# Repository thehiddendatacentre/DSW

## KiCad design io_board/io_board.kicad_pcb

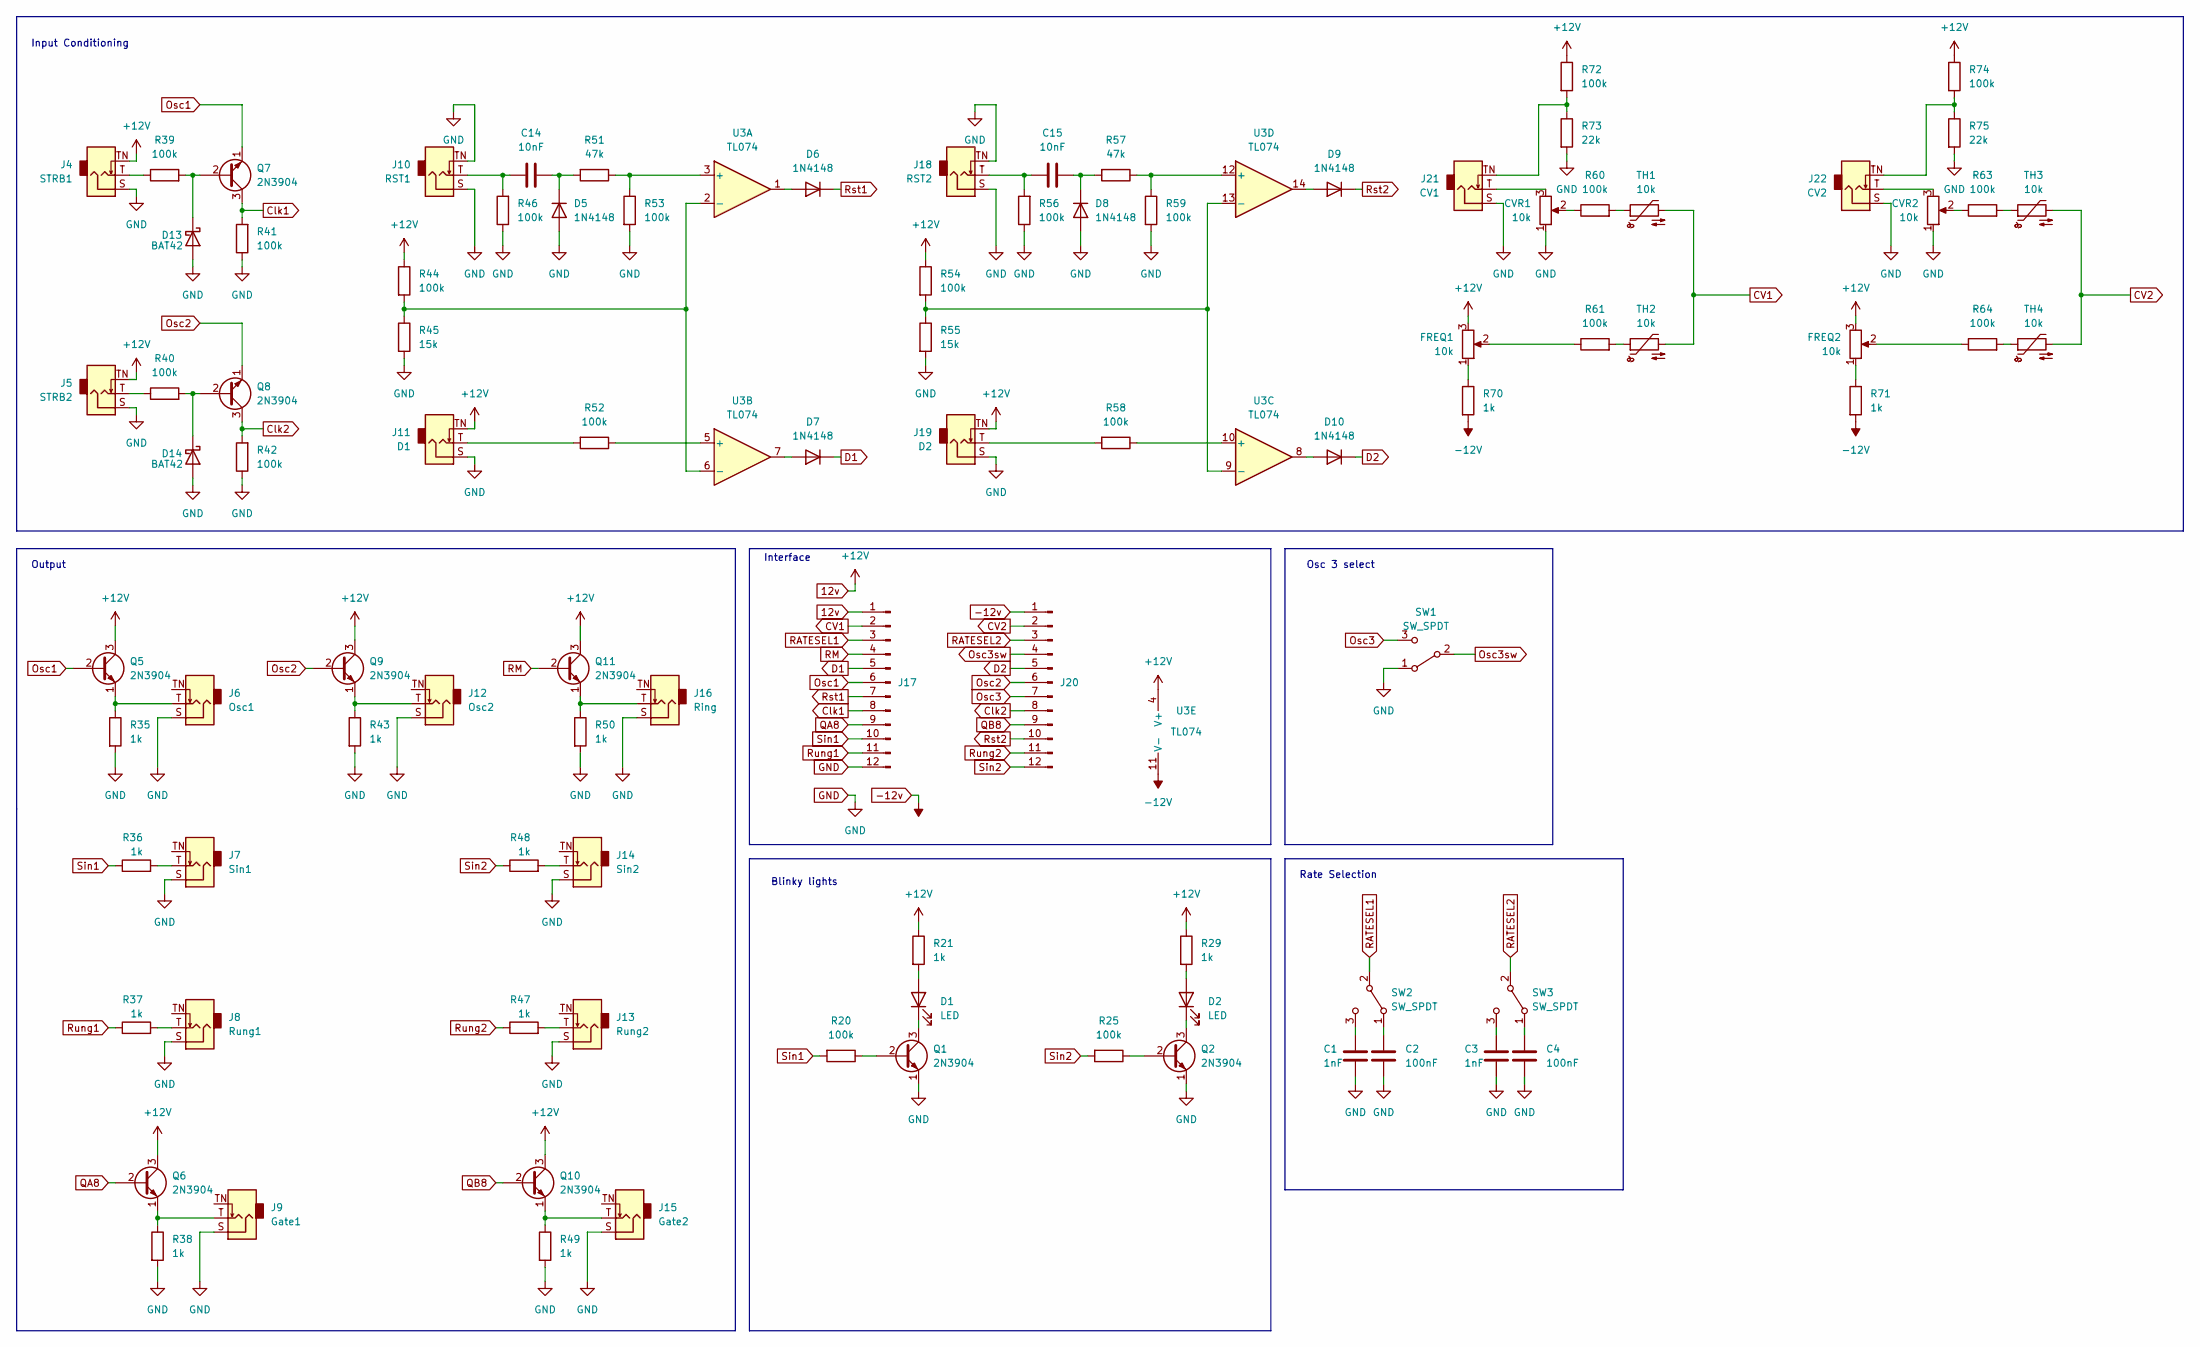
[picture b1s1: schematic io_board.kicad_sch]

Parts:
C1, C3: 1nF; C_Disc_D5.0mm_W2.5mm_P2.50mm
C2, C4: 100nF; C_Disc_D5.0mm_W2.5mm_P2.50mm
C14, C15: 10nF; C_Disc_D5.0mm_W2.5mm_P2.50mm
CVR1, CVR2: 10k; Potentiometer_Alpha_R0904N
D1, D2: LED; LED_D3.0mm
D5, D6, D7, D8, D9, D10: 1N4148; D_DO-35_SOD27_P7.62mm_Horizontal
D13, D14: BAT42; D_DO-35_SOD27_P7.62mm_Horizontal
FREQ1, FREQ2: 10k; Potentiometer_Alpha_R0904N
J4: STRB1; AudioJack_WQP518MA
J5: STRB2; AudioJack_WQP518MA
J6: Osc1; AudioJack_WQP518MA
J7: Sin1; AudioJack_WQP518MA
J8: Rung1; AudioJack_WQP518MA
J9: Gate1; AudioJack_WQP518MA
J10: RST1; AudioJack_WQP518MA
J11: D1; AudioJack_WQP518MA
J12: Osc2; AudioJack_WQP518MA
J13: Rung2; AudioJack_WQP518MA
J14: Sin2; AudioJack_WQP518MA
J15: Gate2; AudioJack_WQP518MA
J16: Ring; AudioJack_WQP518MA
J17, J20: PinHeader_1x12_P2.54mm_Vertical
J18: RST2; AudioJack_WQP518MA
J19: D2; AudioJack_WQP518MA
J21: CV1; AudioJack_WQP518MA
J22: CV2; AudioJack_WQP518MA
Q1, Q2, Q5, Q6, Q7, Q8, Q9, Q10, Q11: 2N3904; TO-92_Inline
R20, R25, R39, R40, R41, R42, R44, R46, R52, R53, R54, R56, R58, R59, R60, R61, R63, R64, R72, R74: 100k; R_Axial_DIN0204_L3.6mm_D1.6mm_P7.62mm_Horizontal
R21, R29, R35, R36, R37, R38, R43, R47, R48, R49, R50, R70, R71: 1k; R_Axial_DIN0204_L3.6mm_D1.6mm_P7.62mm_Horizontal
R45, R55: 15k; R_Axial_DIN0204_L3.6mm_D1.6mm_P7.62mm_Horizontal
R51, R57: 47k; R_Axial_DIN0204_L3.6mm_D1.6mm_P7.62mm_Horizontal
R73, R75: 22k; R_Axial_DIN0204_L3.6mm_D1.6mm_P7.62mm_Horizontal
SW1, SW2, SW3: SW_SPDT; Miniature_Switch_SPDT_2.54MM
TH1, TH2, TH3, TH4: 10k; R_Axial_DIN0204_L3.6mm_D1.6mm_P2.54mm_Vertical
U3: TL074; DIP-14_W7.62mm_Socket_LongPads

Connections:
12v: FREQ1.3, FREQ2.3, J4.TN, J5.TN, J11.TN, J17.1, J19.TN, Q5.3 (C), Q6.3 (C), Q9.3 (C), Q10.3 (C), Q11.3 (C), R21.1, R29.1, R44.1, R54.1, R72.1, R74.1, U3.4 (V+)
-12v: J20.1, R70.2, R71.2, U3.11 (V-)
CV1: J17.2, TH1.2, TH2.2
CV2: J20.2, TH3.2, TH4.2
Clk1: J17.8, Q7.3 (C), R41.2
Clk2: J20.8, Q8.3 (C), R42.2
D1: D7.1 (K), J17.5
D2: D10.1 (K), J20.5
GND: C1.2, C2.2, C3.2, C4.2, CVR1.1, CVR2.1, D5.2 (A), D8.2 (A), D13.2 (A), D14.2 (A), J4.S, J5.S, J6.S, J7.S, J8.S, J9.S, J10.S, J10.TN, J11.S, J12.S, J13.S, J14.S, J15.S, J16.S, J17.12, J18.S, J18.TN, J19.S, J21.S, J22.S, Q1.1 (E), Q2.1 (E), R35.2, R38.2, R41.1, R42.1, R43.2, R45.2, R46.1, R49.2, R50.2, R53.2, R55.2, R56.1, R59.2, R73.2, R75.2, SW1.1 (A)
unnamed: C1.1, SW2.3 (C)
unnamed: C2.1, SW2.1 (A)
unnamed: C3.1, SW3.3 (C)
unnamed: C4.1, SW3.1 (A)
unnamed: C14.1, D5.1 (K), R51.2
unnamed: C14.2, J10.T, R46.2
unnamed: C15.1, D8.1 (K), R57.2
unnamed: C15.2, J18.T, R56.2
unnamed: CVR1.2, R60.1
unnamed: CVR1.3, J21.T
unnamed: CVR2.2, R63.1
unnamed: CVR2.3, J22.T
unnamed: D1.1 (K), Q1.3 (C)
unnamed: D1.2 (A), R21.2
unnamed: D2.1 (K), Q2.3 (C)
unnamed: D2.2 (A), R29.2
unnamed: D6.2 (A), U3.1
unnamed: D7.2 (A), U3.7
unnamed: D9.2 (A), U3.14
unnamed: D10.2 (A), U3.8
unnamed: D13.1 (K), Q7.2 (B), R39.2
unnamed: D14.1 (K), Q8.2 (B), R40.2
unnamed: FREQ1.1, R70.1
unnamed: FREQ1.2, R61.1
unnamed: FREQ2.1, R71.1
unnamed: FREQ2.2, R64.1
unnamed: J4.T, R39.1
unnamed: J5.T, R40.1
unnamed: J6.T, Q5.1 (E), R35.1
unnamed: J7.T, R36.2
unnamed: J8.T, R37.2
unnamed: J9.T, Q6.1 (E), R38.1
unnamed: J11.T, R52.2
unnamed: J12.T, Q9.1 (E), R43.1
unnamed: J13.T, R47.2
unnamed: J14.T, R48.2
unnamed: J15.T, Q10.1 (E), R49.1
unnamed: J16.T, Q11.1 (E), R50.1
unnamed: J19.T, R58.2
unnamed: J21.TN, R72.2, R73.1
unnamed: J22.TN, R74.2, R75.1
unnamed: Q1.2 (B), R20.1
unnamed: Q2.2 (B), R25.1
unnamed: R44.2, R45.1, U3.2 (-), U3.6 (-)
unnamed: R51.1, R53.1, U3.3 (+)
unnamed: R52.1, U3.5 (+)
unnamed: R54.2, R55.1, U3.9 (-), U3.13 (-)
unnamed: R57.1, R59.1, U3.12 (+)
unnamed: R58.1, U3.10 (+)
unnamed: R60.2, TH1.1
unnamed: R61.2, TH2.1
unnamed: R63.2, TH3.1
unnamed: R64.2, TH4.1
Osc1: J17.6, Q5.2 (B), Q7.1 (E)
Osc2: J20.6, Q8.1 (E), Q9.2 (B)
Osc3: J20.7, SW1.3 (C)
Osc3sw: J20.4, SW1.2 (B)
QA8: J17.9, Q6.2 (B)
QB8: J20.9, Q10.2 (B)
RATESEL1: J17.3, SW2.2 (B)
RATESEL2: J20.3, SW3.2 (B)
RM: J17.4, Q11.2 (B)
Rst1: D6.1 (K), J17.7
Rst2: D9.1 (K), J20.10
Rung1: J17.11, R37.1
Rung2: J20.11, R47.1
Sin1: J17.10, R20.2, R36.1
Sin2: J20.12, R25.2, R48.1

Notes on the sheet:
Osc 3 select
Blinky lights
Rate Selection
Output
Input Conditioning
Interface

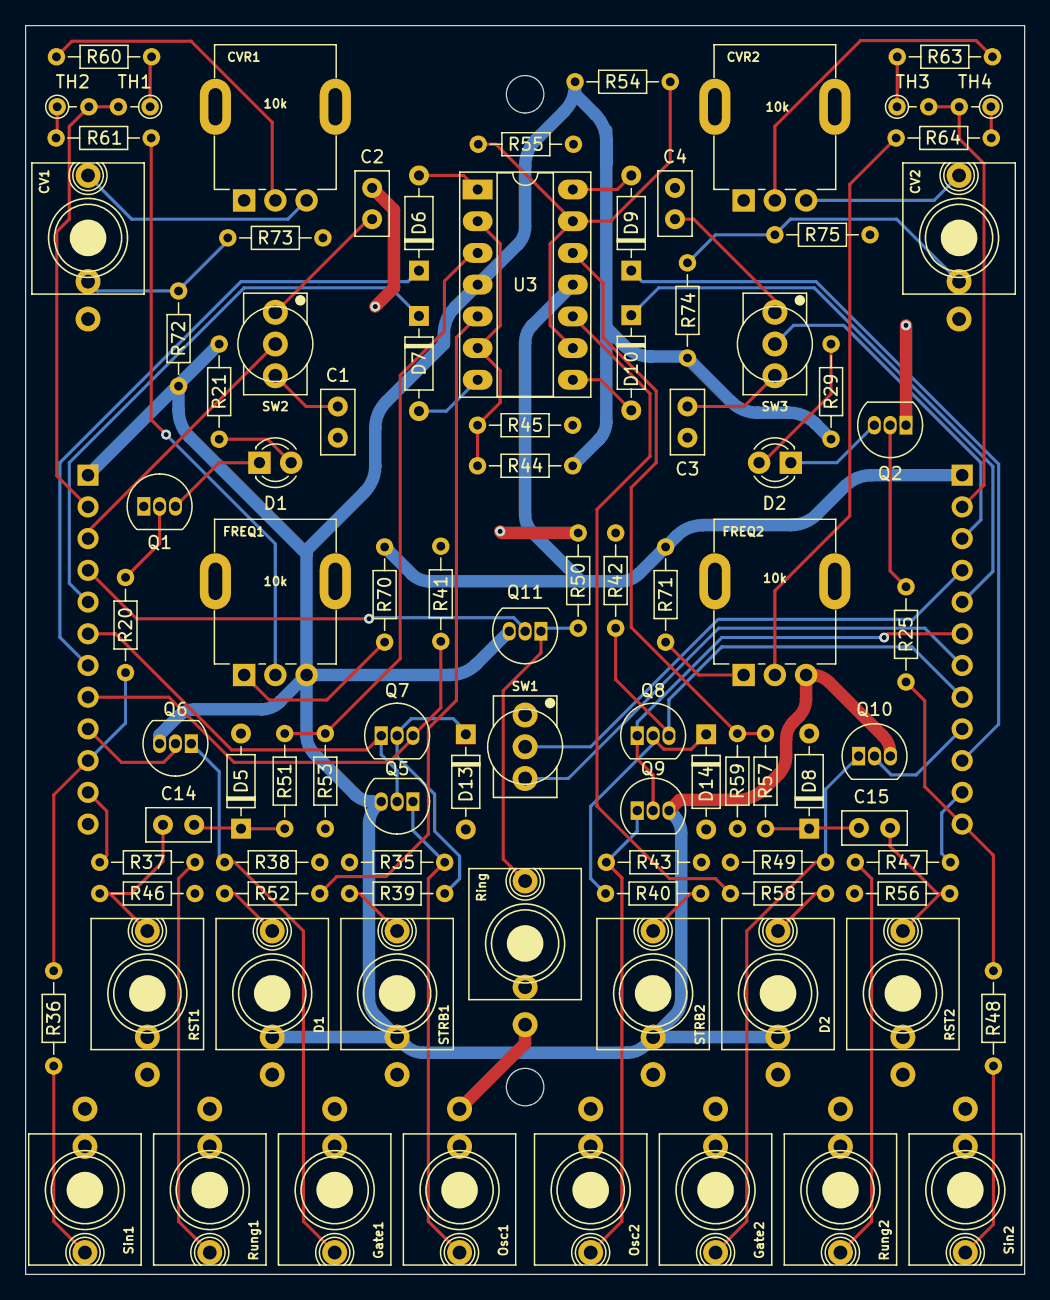
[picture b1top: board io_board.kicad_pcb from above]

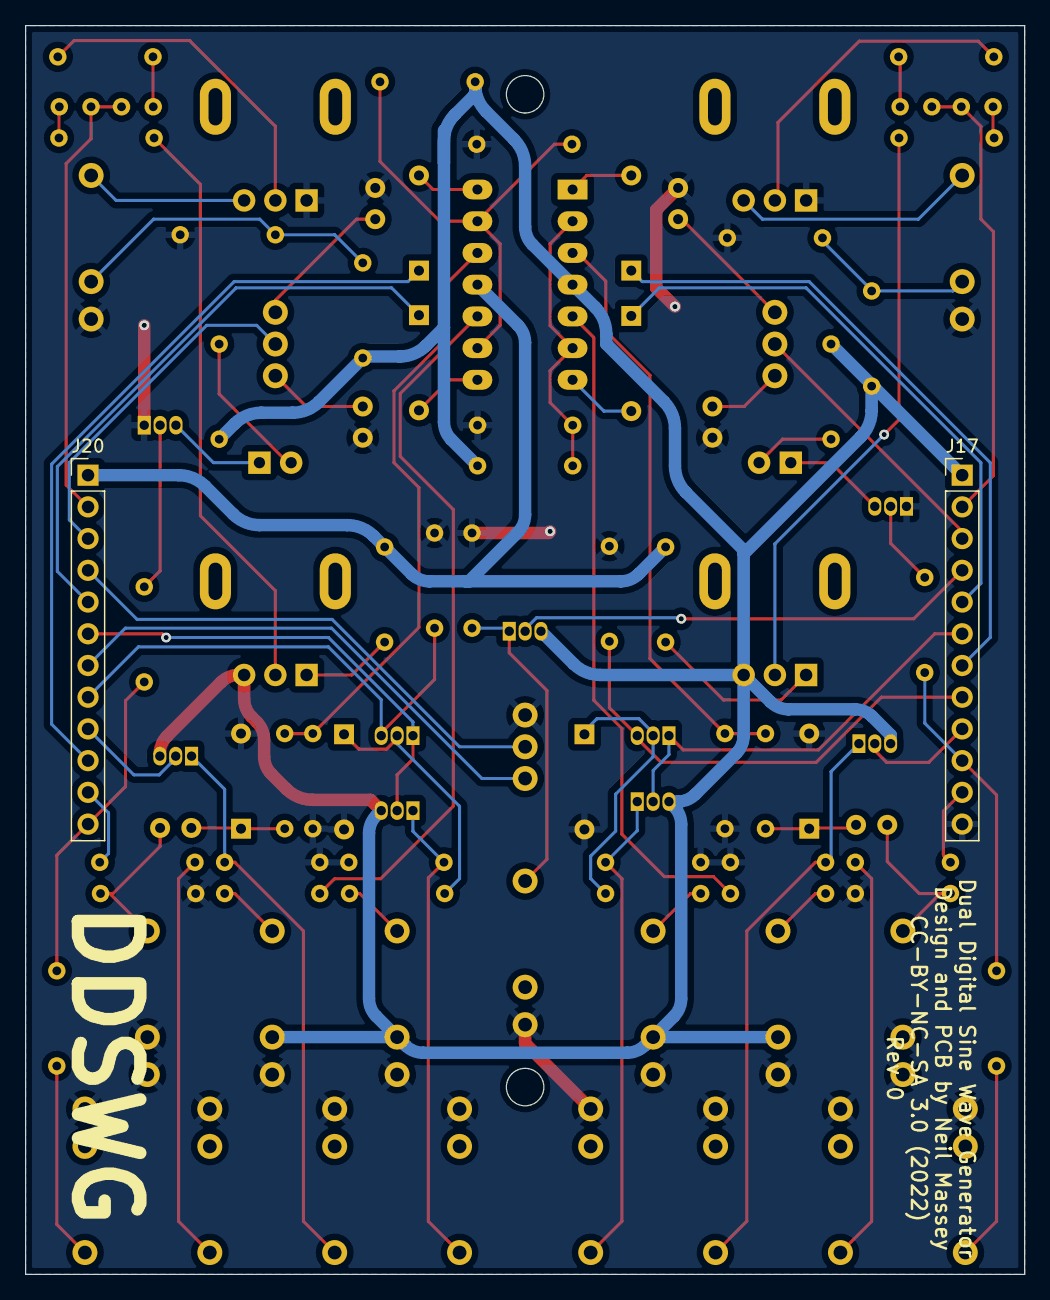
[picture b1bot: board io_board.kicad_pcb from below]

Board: 2 copper layers, 80.0 x 100.0 mm, 95 parts (2 on the bottom side), 77 nets.

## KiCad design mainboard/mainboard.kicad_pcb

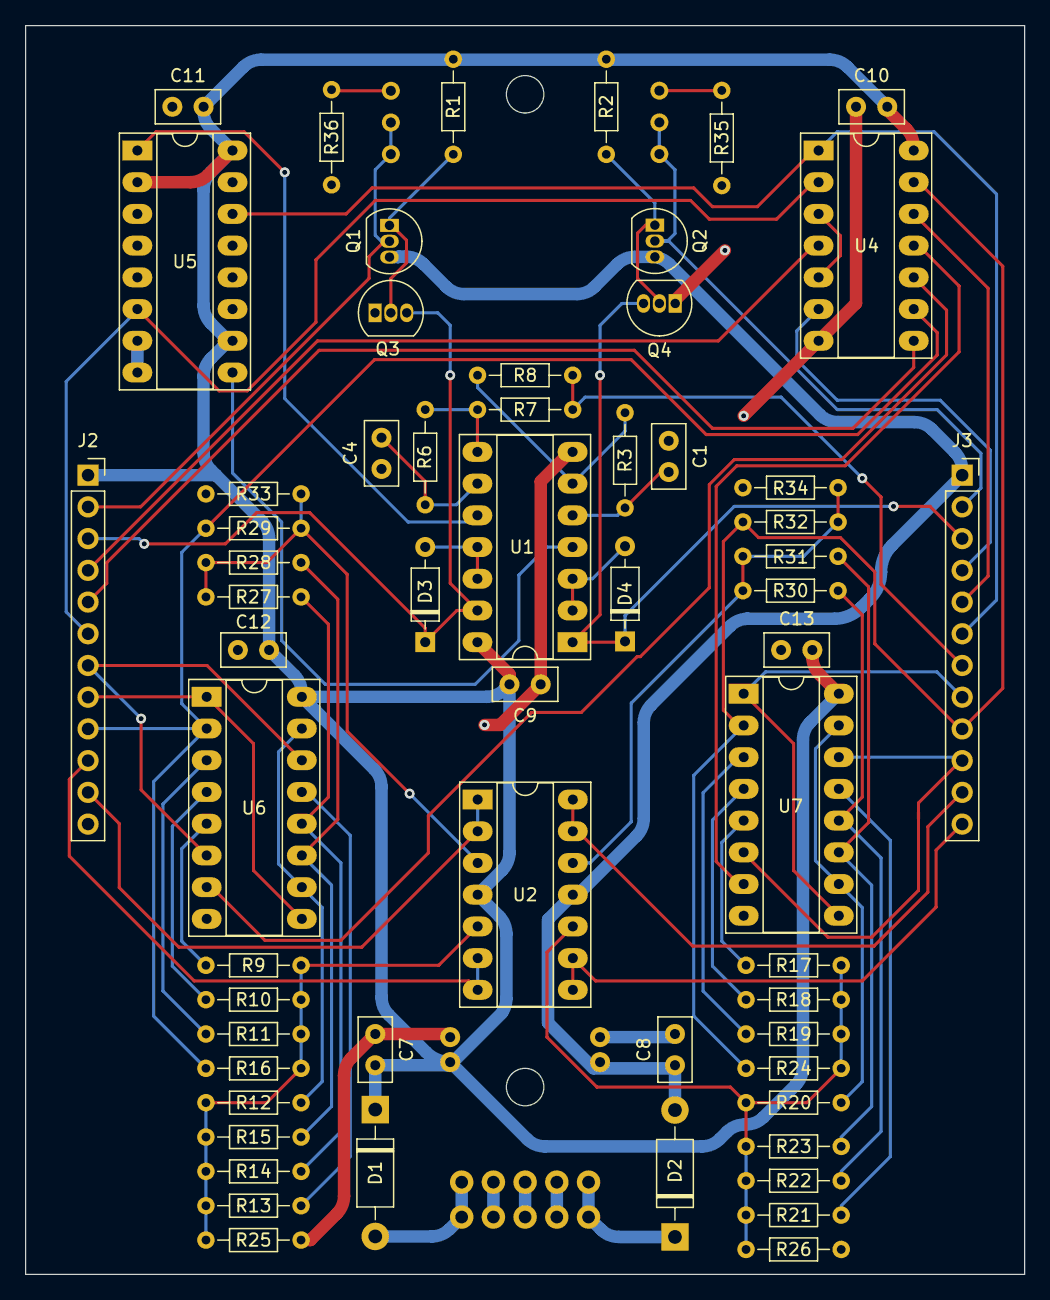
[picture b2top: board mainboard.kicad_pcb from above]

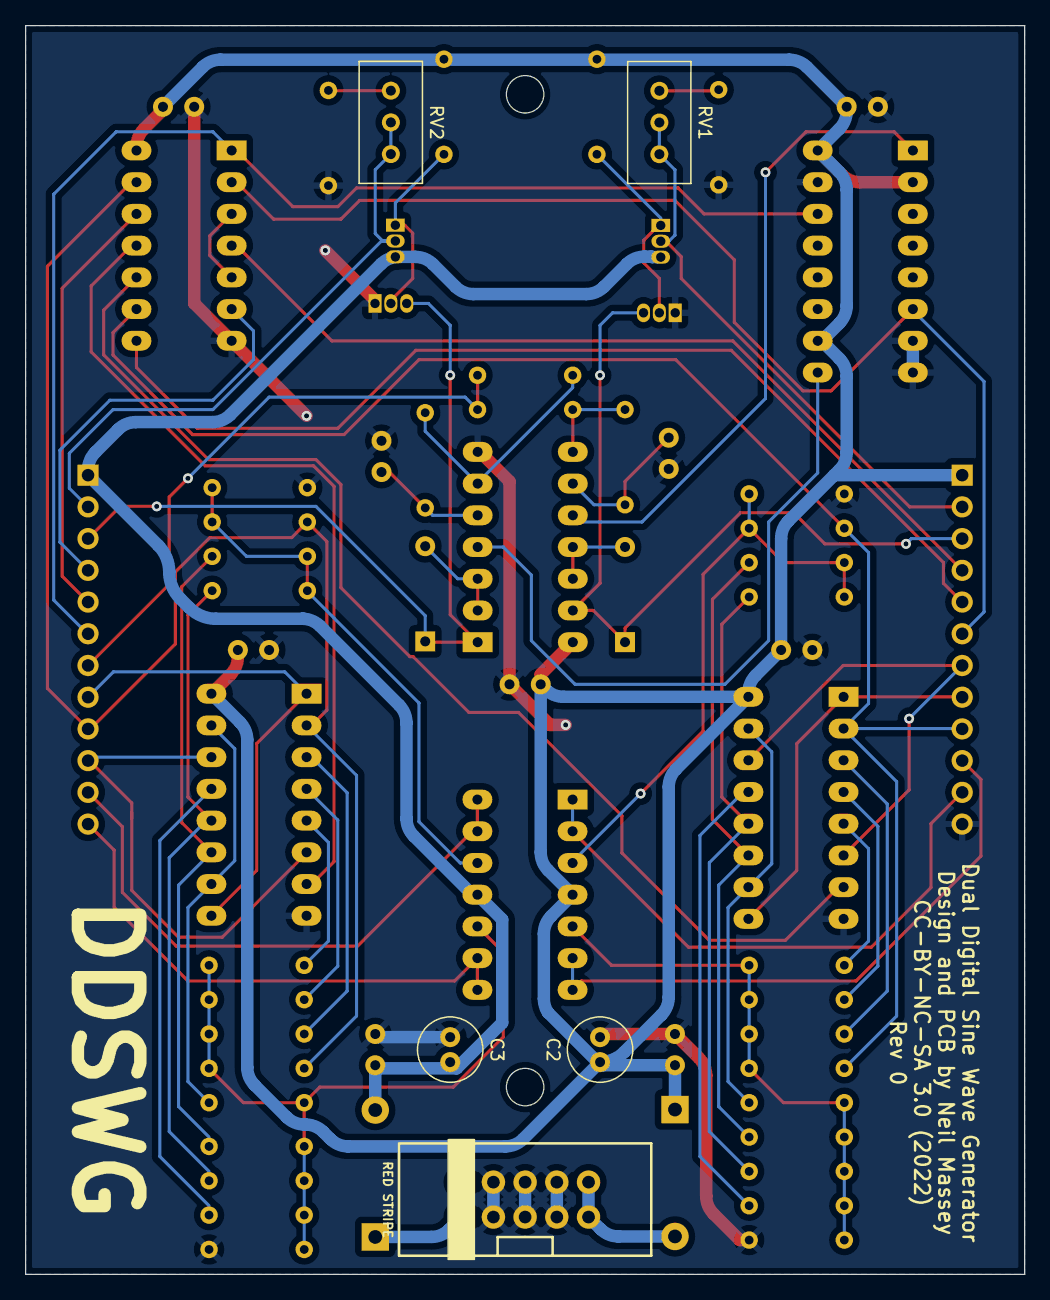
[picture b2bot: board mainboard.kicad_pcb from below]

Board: 2 copper layers, 80.0 x 100.0 mm, 64 parts (5 on the bottom side), 59 nets.

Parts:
C1, C4: 10nF; C_Disc_D5.0mm_W2.5mm_P2.50mm
C2, C3: 10uF; C_Radial_D5.0mm_H11.0mm_P2.00mm
C7, C8, C9, C10, C11, C12, C13: 100nF; C_Disc_D5.0mm_W2.5mm_P2.50mm
D1, D2: 1N4001; D_DO-41_SOD81_P10.16mm_Horizontal
D3, D4: 1N4148; D_DO-35_SOD27_P7.62mm_Horizontal
J1: Eurorack_Power; Eurorack_Power_2x5_Shrouded
J2: Osc1_Socket; PinSocket_1x12_P2.54mm_Vertical
J3: Osc2_Socket; PinSocket_1x12_P2.54mm_Vertical
Q1, Q2: 2N3906; TO-92_Inline
Q3, Q4: 2N3904; TO-92_Inline
R1, R2: 1M; R_Axial_DIN0204_L3.6mm_D1.6mm_P7.62mm_Horizontal
R3: 1Meg; R_Axial_DIN0204_L3.6mm_D1.6mm_P7.62mm_Horizontal
R6, R10, R16, R18, R24: 330k; R_Axial_DIN0204_L3.6mm_D1.6mm_P7.62mm_Horizontal
R7, R8, R13, R21, R25, R26, R27, R30, R33, R34: 100k; R_Axial_DIN0204_L3.6mm_D1.6mm_P7.62mm_Horizontal
R9, R17: 470k; R_Axial_DIN0204_L3.6mm_D1.6mm_P7.62mm_Horizontal
R11, R15, R19, R23: 220k; R_Axial_DIN0204_L3.6mm_D1.6mm_P7.62mm_Horizontal
R12, R14, R20, R22: 150k; R_Axial_DIN0204_L3.6mm_D1.6mm_P7.62mm_Horizontal
R28, R31: 47k; R_Axial_DIN0204_L3.6mm_D1.6mm_P7.62mm_Horizontal
R29, R32: 22k; R_Axial_DIN0204_L3.6mm_D1.6mm_P7.62mm_Horizontal
R35, R36: 1.5k; R_Axial_DIN0204_L3.6mm_D1.6mm_P7.62mm_Horizontal
RV1, RV2: 1k; Potentiometer_Bourns_3296W_Vertical
U1: 40106; DIP-14_W7.62mm_Socket_LongPads
U2: TL074; DIP-14_W7.62mm_Socket_LongPads
U4: 4070; DIP-14_W7.62mm_Socket_LongPads
U5: 4520; DIP-16_W7.62mm_Socket_LongPads
U6, U7: 4015; DIP-16_W7.62mm_Socket_LongPads

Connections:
12v: C2.1, C7.2, C9.1, C10.1, C11.1, C12.1, C13.1, D1.1 (K), J2.1, R1.1, R2.1, U1.14 (VDD), U2.4 (V+), U4.14 (VDD), U5.2 (Enable), U5.10 (Enable), U5.16 (VDD), U6.16 (Vdd), U7.16 (Vdd)
-12v: C3.2, C8.2, D2.2 (A), J3.1, Q1.3 (C), Q2.3 (C), U2.11 (V-)
CV1: J2.2, Q1.2 (B), RV1.1, RV1.2
CV2: J3.2, Q2.2 (B), RV2.1, RV2.2
Clk1: J2.8, U6.1 (CP), U6.9 (CP)
Clk2: J3.8, U7.1 (CP), U7.9 (CP)
D1: J2.5, U4.8
D2: J3.5, U4.12
GND: C1.1, C2.2, C3.1, C4.1, C7.1, C8.1, C9.2, C10.2, C11.2, C12.2, C13.2, J1.3 (GND), J1.4 (GND), J1.5 (GND), J1.6 (GND), J1.7 (GND), J1.8 (GND), J2.12, Q3.1 (E), Q4.1 (E), R25.1, R26.1, R33.1, R34.1, R35.2, R36.2, U1.7 (VSS), U4.7 (VSS), U5.7 (Reset), U5.8 (VSS), U5.15 (Reset), U6.8 (Vss), U7.8 (Vss)
unnamed: C1.2, R3.1, U1.5
unnamed: C4.2, R6.1, U1.9
unnamed: D1.2 (A), J1.9 (+12V), J1.10 (+12V)
unnamed: D2.1 (K), J1.1 (-12V), J1.2 (-12V)
unnamed: D3.2 (A), U1.11, U1.12
unnamed: D4.2 (A), U1.2, U1.3
unnamed: Q1.1 (E), Q3.2 (B), R1.2
unnamed: Q2.1 (E), Q4.2 (B), R2.2
unnamed: R3.2, R8.1, U1.6
unnamed: R6.2, R7.1, U1.8
unnamed: R9.2, R10.2, R11.2, R12.2, R13.2, R14.2, R15.2, R16.2, R25.2, U2.5 (+)
unnamed: R17.2, R18.2, R19.2, R20.2, R21.2, R22.2, R23.2, R24.2, R26.2, U2.10 (+)
unnamed: R27.2, R28.2, R29.2, R33.2, U2.3 (+)
unnamed: R30.2, R31.2, R32.2, R34.2, U2.12 (+)
unnamed: R35.1, RV2.3
unnamed: R36.1, RV1.3
unnamed: U4.3, U4.5
unnamed: U4.10, U6.7 (D)
unnamed: U4.11, U7.7 (D)
O1: U1.10, U5.1 (CK)
O2: U1.4, U5.9 (CK)
Osc1: J2.6, U4.2, U5.6 (Q4)
Osc2: J3.6, U4.1, U5.14 (Q4)
Osc3: J3.7, R7.2, R8.2
Osc3sw: J3.4, U4.6
QA1: R9.1, U6.5 (Q1)
QA2: R10.1, U6.4 (Q2)
QA3: R11.1, U6.3 (Q3)
QA4: R12.1, U6.10 (Q4), U6.15 (D)
QA5: R13.1, U6.13 (Q1)
QA6: R14.1, R27.1, U6.12 (Q2)
QA7: R15.1, R28.1, U6.11 (Q3)
QA8: J2.9, R16.1, R29.1, U4.9, U6.2 (Q4)
QB1: R17.1, U7.5 (Q1)
QB2: R18.1, U7.4 (Q2)
QB3: R19.1, U7.3 (Q3)
QB4: R20.1, U7.10 (Q4), U7.15 (D)
QB5: R21.1, U7.13 (Q1)
QB6: R22.1, R30.1, U7.12 (Q2)
QB7: R23.1, R31.1, U7.11 (Q3)
QB8: J3.9, R24.1, R32.1, U4.13, U7.2 (Q4)
RATESEL1: D3.1 (K), J2.3, Q3.3 (C), U1.13
RATESEL2: D4.1 (K), J3.3, Q4.3 (C), U1.1
RM: J2.4, U4.4
Rst1: J2.7, U6.6 (MR), U6.14 (MR)
Rst2: J3.10, U7.6 (MR), U7.14 (MR)
Rung1: J2.11, U2.1, U2.2 (-)
Rung2: J3.11, U2.13 (-), U2.14
Sin1: J2.10, U2.6 (-), U2.7
Sin2: J3.12, U2.8, U2.9 (-)

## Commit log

2022-11-18 Added LICENSE.md
2022-11-26 Routing done, panel done
2022-11-26 Rejigged layout for more space
2022-11-28 Updates to panel etc.
2023-01-27 Removed the unneccessary 100ohm resistor after the expo converter
2023-02-01 Added negative CV protection diodes
2023-02-02 Flip flop on CV protection diodes
2023-02-26 Added range switch

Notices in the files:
io_board/io_board.kicad_pcb:
CC-BY-NC-SA 3.0 (2022)
